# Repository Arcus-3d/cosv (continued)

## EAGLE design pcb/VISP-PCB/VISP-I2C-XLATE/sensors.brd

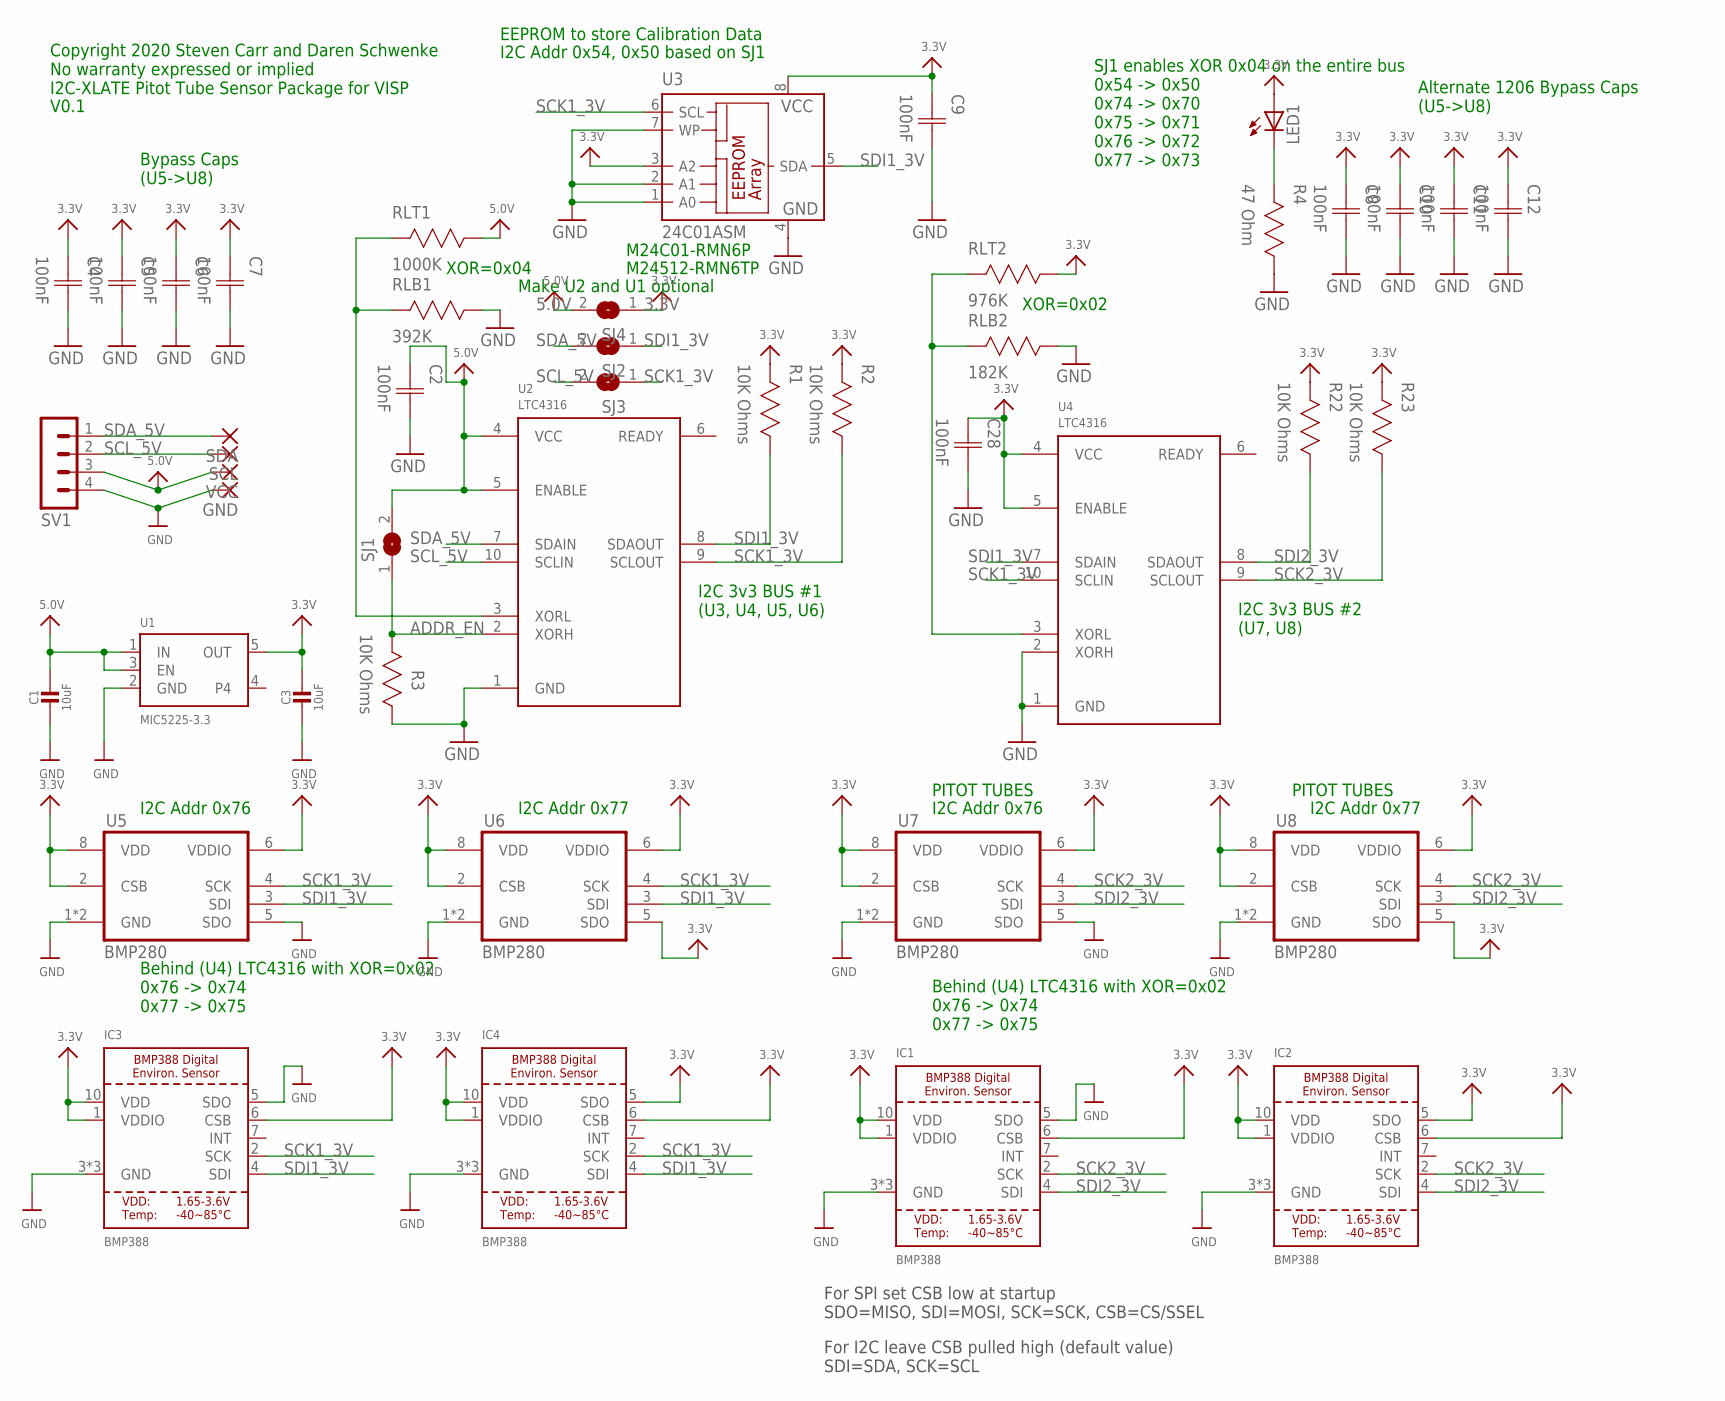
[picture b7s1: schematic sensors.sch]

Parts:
C1, C3: 10uF; 0603-NO; MPN C1608X5R1A106M080AC
C2, C9, C28: 100nF; CAP0603; MPN CL10B104KB8NNNC
C4, C5, C6, C7: 100nF; CAP0402; MPN CL10F104ZO8NNNC
C8, C10, C11, C12: 100nF; CAP1206; MPN C1206C104K5RAC7800
GND: SMD2; SMD1,27-2,54
IC1, IC2, IC3, IC4: BMP388; MPN BMP388
LED1: LEDCHIP-LED0603; CHIP-LED0603; MPN SML-D12P8WT86
R1, R2, R22, R23: 10K Ohms; RES0603; MPN CRCW060310K0FKEAC
R3: 10K Ohms; RES0603; MPN CL10B104KB8NNNC
R4: 47 Ohm; RES0603; MPN RC0603FR-0747RL
RLB1: 392K; RES0603; MPN RC0603FR-07392KL
RLB2: 182K; RES0603; MPN RC0603FR-07182KL
RLT1: 1000K; RES0603; MPN CRCW060310K0FKEAC
RLT2: 976K; RES0603; MPN RC0603FR-07976KL
SCL: SMD2; SMD1,27-2,54
SDA: SMD2; SMD1,27-2,54
SJ1, SJ2, SJ3, SJ4: SJ
SV1: MA04-1
U1: MIC5225-3.3; SOT23-5; MPN MIC5225-3.3YM5-TR
U2, U4: LTC4316; MSOP10; MPN LTC4316IMS#PBF
U3: 24C01ASM; SO-08M; MPN M24C01-RMN6P
U5, U6, U7, U8: BMP280; MPN BMP280
VCC: SMD2; SMD1,27-2,54

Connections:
3.3V: C3.1, C4.1 (C1), C5.1 (C1), C6.1 (C1), C7.1 (C1), C8.1 (C1), C9.1 (C1), C10.1 (C1), C11.1 (C1), C12.1 (C1), C28.1 (C1), IC1.1 (VDDIO), IC1.6 (CSB), IC1.10 (VDD), IC2.1 (VDDIO), IC2.5 (SDO), IC2.6 (CSB), IC2.10 (VDD), IC3.1 (VDDIO), IC3.6 (CSB), IC3.10 (VDD), IC4.1 (VDDIO), IC4.5 (SDO), IC4.6 (CSB), IC4.10 (VDD), LED1.A, R1.2, R2.2, R22.2, R23.2, RLT2.1, SJ4.1, U1.5 (OUT), U3.3 (A2), U3.8 (VCC), U4.4 (VCC), U4.5 (ENABLE), U5.2 (CSB), U5.6 (VDDIO), U5.8 (VDD), U6.2 (CSB), U6.5 (SDO), U6.6 (VDDIO), U6.8 (VDD), U7.2 (CSB), U7.6 (VDDIO), U7.8 (VDD), U8.2 (CSB), U8.5 (SDO), U8.6 (VDDIO), U8.8 (VDD)
5.0V: C1.1, C2.1 (C1), RLT1.1, SJ1.2, SJ4.2, SV1.3, U1.1 (IN), U1.3 (EN), U2.4 (VCC), U2.5 (ENABLE), VCC.1
ADDR_EN: R3.2, SJ1.1, U2.2 (XORH)
GND: C1.2, C2.2 (C2), C3.2, C4.2 (C2), C5.2 (C2), C6.2 (C2), C7.2 (C2), C8.2 (C2), C9.2 (C2), C10.2 (C2), C11.2 (C2), C12.2 (C2), C28.2 (C2), GND.1, IC1.3 (GND), IC1.5 (SDO), IC1.8 (GND), IC1.9 (GND), IC2.3 (GND), IC2.8 (GND), IC2.9 (GND), IC3.3 (GND), IC3.5 (SDO), IC3.8 (GND), IC3.9 (GND), IC4.3 (GND), IC4.8 (GND), IC4.9 (GND), R3.1, R4.1, RLB1.1, RLB2.1, SV1.4, U1.2 (GND), U2.1 (GND), U3.1 (A0), U3.2 (A1), U3.4 (GND), U3.7 (WP), U4.1 (GND), U4.2 (XORH), U5.1 (GND), U5.5 (SDO), U5.7 (GND), U6.1 (GND), U6.7 (GND), U7.1 (GND), U7.5 (SDO), U7.7 (GND), U8.1 (GND), U8.7 (GND)
LED: LED1.C, R4.2
SCK1_3V: IC3.2 (SCK), IC4.2 (SCK), R2.1, SJ3.1, U2.9 (SCLOUT), U3.6 (SCL), U4.10 (SCLIN), U5.4 (SCK), U6.4 (SCK)
SCK2_3V: IC1.2 (SCK), IC2.2 (SCK), R23.1, U4.9 (SCLOUT), U7.4 (SCK), U8.4 (SCK)
SCL_5V: SCL.1, SJ3.2, SV1.2, U2.10 (SCLIN)
SDA_5V: SDA.1, SJ2.2, SV1.1, U2.7 (SDAIN)
SDI1_3V: IC3.4 (SDI), IC4.4 (SDI), R1.1, SJ2.1, U2.8 (SDAOUT), U3.5 (SDA), U4.7 (SDAIN), U5.3 (SDI), U6.3 (SDI)
SDI2_3V: IC1.4 (SDI), IC2.4 (SDI), R22.1, U4.8 (SDAOUT), U7.3 (SDI), U8.3 (SDI)
XORL1: RLB1.2, RLT1.2, U2.3 (XORL)
XORL2: RLB2.2, RLT2.2, U4.3 (XORL)

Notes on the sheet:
XOR=0x02
XOR=0x04
Bypass Caps (U5->U8)
Copyright 2020 Steven Carr and Daren Schwenke No warranty expressed or implied I2C-XLATE Pitot Tube Sensor Package for VISP
EEPROM to store Calibration Data
I2C Addr 0x54, 0x50 based on SJ1
I2C Addr 0x76
I2C Addr 0x77
Behind (U4) LTC4316 with XOR=0x02 0x76 -> 0x74 0x77 -> 0x75
SJ1 enables XOR 0x04 on the entire bus 0x54 -> 0x50 0x74 -> 0x70 0x75 -> 0x71 0x76 -> 0x72 0x77 -> 0x73
I2C 3v3 BUS #1 (U3, U4, U5, U6)
I2C 3v3 BUS #2 (U7, U8)
V0.1
Make U2 and U1 optional
PITOT TUBES
For SPI set CSB low at startup SDO=MISO, SDI=MOSI, SCK=SCK, CSB=CS/SSEL
For I2C leave CSB pulled high (default value) SDI=SDA, SCK=SCL
Alternate 1206 Bypass Caps (U5->U8)
M24C01-RMN6P
M24512-RMN6TP

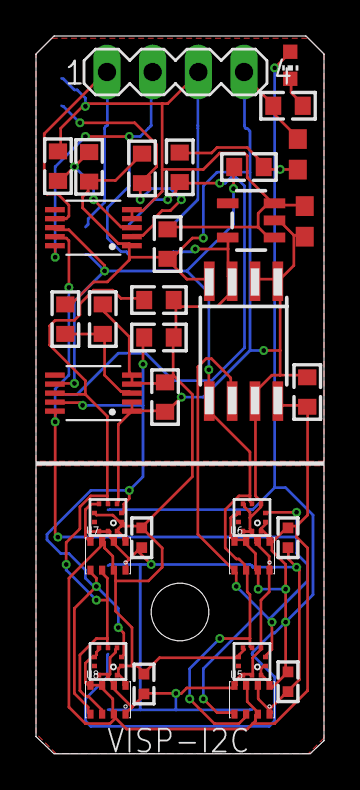
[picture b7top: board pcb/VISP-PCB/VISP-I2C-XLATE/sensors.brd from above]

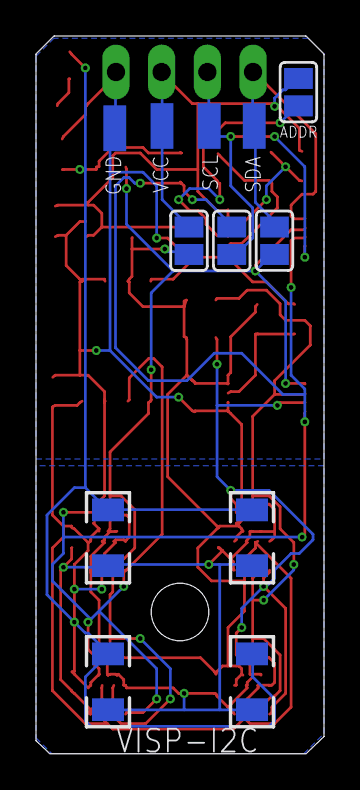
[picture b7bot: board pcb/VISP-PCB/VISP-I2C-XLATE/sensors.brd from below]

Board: 2 copper layers, 16.0 x 39.9 mm, 45 parts (12 on the bottom side), 13 nets.

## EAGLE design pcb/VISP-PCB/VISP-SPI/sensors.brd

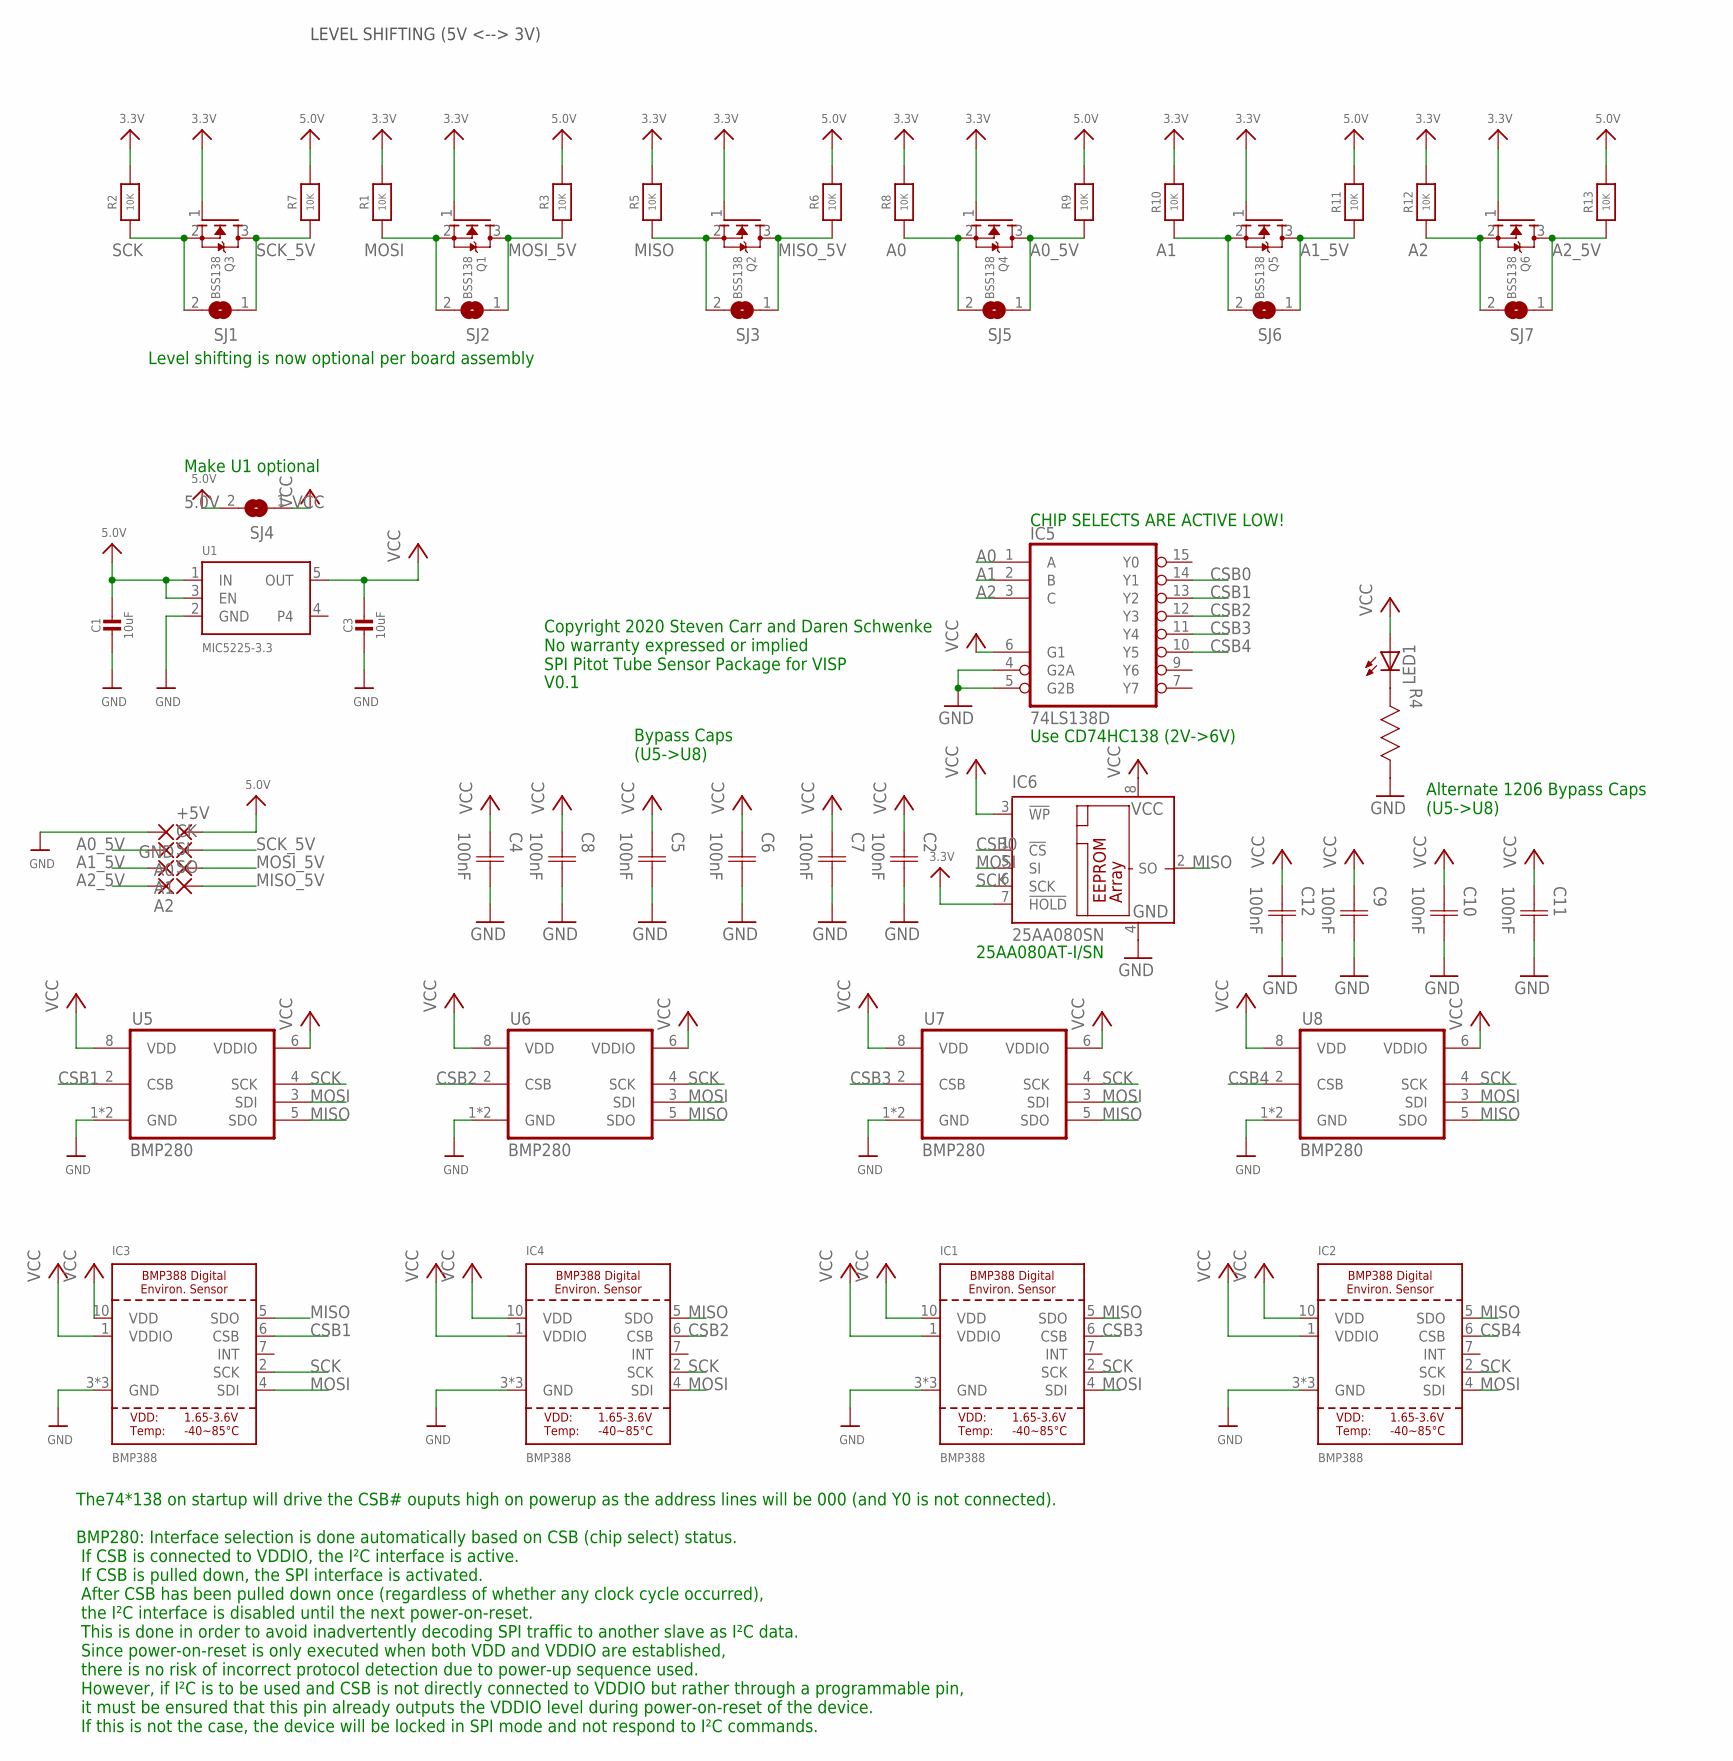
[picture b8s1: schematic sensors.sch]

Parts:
+5V: SMD2; SMD1,27-2,54
A0, A1, A2: SMD2; SMD1,27-2,54
C1, C3: 10uF; 0603-NO
C2, C4, C5, C6, C7, C8: 100nF; CAP0402
C9, C10, C11, C12: 100nF; CAP1206
CK: SMD2; SMD1,27-2,54
GND: SMD2; SMD1,27-2,54
IC1, IC2, IC3, IC4: BMP388
IC5: 74LS138D; SO16; MPN CD74LS138D
IC6: 25AA080SN; SO-08
LED1: LEDCHIP-LED0603; CHIP-LED0603
Q1, Q2, Q3, Q4, Q5, Q6: BSS138; SOT23-WIDE
R1, R2, R3, R5, R6, R7, R8, R9, R10, R11, R12, R13: 10K; 0805-NO
R4: RESISTOR-0603; RES0603
SI: SMD2; SMD1,27-2,54
SJ1, SJ2, SJ3, SJ4, SJ5, SJ6, SJ7: SJ
SO: SMD2; SMD1,27-2,54
U1: MIC5225-3.3; SOT23-5
U5, U6, U7, U8: BMP280

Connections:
3.3V: IC6.7 (!HOLD), Q1.1 (G), Q2.1 (G), Q3.1 (G), Q4.1 (G), Q5.1 (G), Q6.1 (G), R1.2, R2.2, R5.2, R8.2, R10.2, R12.2
5.0V: +5V.1, C1.1, R3.2, R6.2, R7.2, R9.2, R11.2, R13.2, SJ4.2, U1.1 (IN), U1.3 (EN)
A0: IC5.1 (A), Q4.2 (S), R8.1, SJ5.2
A0_5V: A0.1, Q4.3 (D), R9.1, SJ5.1
A1: IC5.2 (B), Q5.2 (S), R10.1, SJ6.2
A1_5V: A1.1, Q5.3 (D), R11.1, SJ6.1
A2: IC5.3 (C), Q6.2 (S), R12.1, SJ7.2
A2_5V: A2.1, Q6.3 (D), R13.1, SJ7.1
CSB0: IC5.14 (Y1), IC6.1 (!CS)
CSB1: IC3.6 (CSB), IC5.13 (Y2), U5.2 (CSB)
CSB2: IC4.6 (CSB), IC5.12 (Y3), U6.2 (CSB)
CSB3: IC1.6 (CSB), IC5.11 (Y4), U7.2 (CSB)
CSB4: IC2.6 (CSB), IC5.10 (Y5), U8.2 (CSB)
GND: C1.2, C2.2 (C2), C3.2, C4.2 (C2), C5.2 (C2), C6.2 (C2), C7.2 (C2), C8.2 (C2), C9.2 (C2), C10.2 (C2), C11.2 (C2), C12.2 (C2), GND.1, IC1.3 (GND), IC1.8 (GND), IC1.9 (GND), IC2.3 (GND), IC2.8 (GND), IC2.9 (GND), IC3.3 (GND), IC3.8 (GND), IC3.9 (GND), IC4.3 (GND), IC4.8 (GND), IC4.9 (GND), IC5.4 (G2A), IC5.5 (G2B), IC5.8 (GND), IC6.4 (GND), R4.1, U1.2 (GND), U5.1 (GND), U5.7 (GND), U6.1 (GND), U6.7 (GND), U7.1 (GND), U7.7 (GND), U8.1 (GND), U8.7 (GND)
MISO: IC1.5 (SDO), IC2.5 (SDO), IC3.5 (SDO), IC4.5 (SDO), IC6.2 (SO), Q2.2 (S), R5.1, SJ3.2, U5.5 (SDO), U6.5 (SDO), U7.5 (SDO), U8.5 (SDO)
MISO_5V: Q2.3 (D), R6.1, SJ3.1, SO.1
MOSI: IC1.4 (SDI), IC2.4 (SDI), IC3.4 (SDI), IC4.4 (SDI), IC6.5 (SI), Q1.2 (S), R1.1, SJ2.2, U5.3 (SDI), U6.3 (SDI), U7.3 (SDI), U8.3 (SDI)
MOSI_5V: Q1.3 (D), R3.1, SI.1, SJ2.1
unnamed: LED1.C, R4.2
SCK: IC1.2 (SCK), IC2.2 (SCK), IC3.2 (SCK), IC4.2 (SCK), IC6.6 (SCK), Q3.2 (S), R2.1, SJ1.2, U5.4 (SCK), U6.4 (SCK), U7.4 (SCK), U8.4 (SCK)
SCK_5V: CK.1, Q3.3 (D), R7.1, SJ1.1
VCC: C2.1 (C1), C3.1, C4.1 (C1), C5.1 (C1), C6.1 (C1), C7.1 (C1), C8.1 (C1), C9.1 (C1), C10.1 (C1), C11.1 (C1), C12.1 (C1), IC1.1 (VDDIO), IC1.10 (VDD), IC2.1 (VDDIO), IC2.10 (VDD), IC3.1 (VDDIO), IC3.10 (VDD), IC4.1 (VDDIO), IC4.10 (VDD), IC5.6 (G1), IC5.16 (VCC), IC6.3 (!WP), IC6.8 (VCC), LED1.A, SJ4.1, U1.5 (OUT), U5.6 (VDDIO), U5.8 (VDD), U6.6 (VDDIO), U6.8 (VDD), U7.6 (VDDIO), U7.8 (VDD), U8.6 (VDDIO), U8.8 (VDD)

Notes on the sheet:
Bypass Caps (U5->U8)
Copyright 2020 Steven Carr and Daren Schwenke No warranty expressed or implied SPI Pitot Tube Sensor Package for VISP
V0.1
Make U1 optional
CHIP SELECTS ARE ACTIVE LOW!
Use CD74HC138 (2V->6V)
Alternate 1206 Bypass Caps (U5->U8)
25AA080AT-I/SN
The74*138 on startup will drive the CSB# ouputs high on powerup as the address lines will be 000 (and Y0 is not connected). BMP280: Interface selection is done automatically based on CSB (chip select) status. If CSB is connected to VDDIO, the I²C interface is active. If CSB is pulled down, the SPI 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
LEVEL SHIFTING (5V <--> 3V)
Level shifting is now optional per board assembly

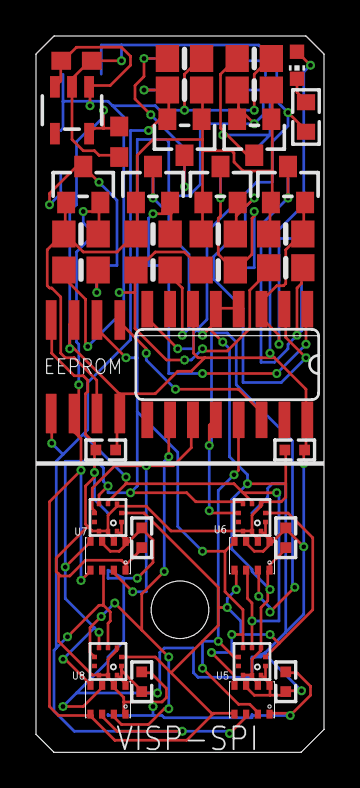
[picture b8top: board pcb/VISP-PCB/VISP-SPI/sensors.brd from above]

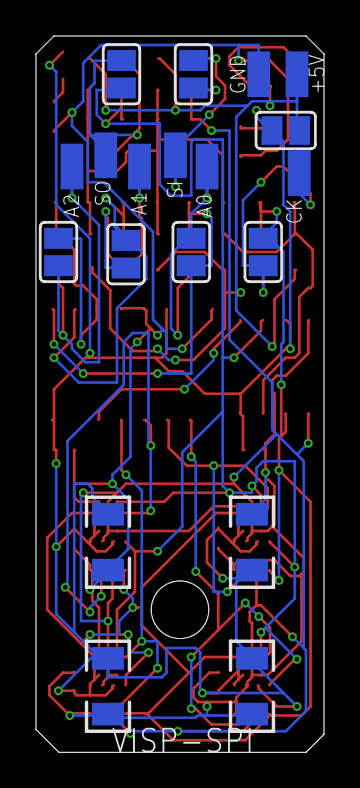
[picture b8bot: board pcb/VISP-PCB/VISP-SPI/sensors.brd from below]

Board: 2 copper layers, 16.0 x 39.8 mm, 58 parts (19 on the bottom side), 22 nets.

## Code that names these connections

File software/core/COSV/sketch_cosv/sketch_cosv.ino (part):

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// A5 - OLED SCL

//
// PD0 - RX - To GUI Processor
// PD1 - TX - To GUI Processor
int VAPE_IN  = 2; // PD2 - IRQ Digital Input - Cheap Vape Sensor (for now)
int BLDC_FG  = 3; // PD3 - IRQ Digital Input - Motor FG
int BLDC_DIR = 4; // PD4 -            - BLDC Motor Direction
int BLDC_PWM = 5; // PD5 - PWM Output - BLDC Motor speed
int WATCHDOG = 6; // PD6 - Watchdog output pulse
int HOME_SENSOR = 7; // PD7 - Digital Input Home Sensor (Pulled up internally, connect other sensor lead to GND)

int STEP_P0 = 8;
int STEP_P1 = 9;
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

//
// PB2 - SS   -
// PB3 - MISO -
// PB4 - MOSI -
// PB5 - SCK  - Also built in uno led...
int LED = 13;

// Hardware
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
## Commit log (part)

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2020-03-25 initial upload
2020-03-25 add gitignore
2020-03-25 moved stuff to allow software
2020-03-25 labeled stuff
2020-03-25 smaller body, less bolts
2020-03-25 softened base corner, rendered for bldc
2020-03-25 renamed output to rendered
2020-03-25 changes for rendering laser files
2020-03-25 bldc motor standoff
2020-03-25 more rendered output files
2020-03-25 more renders
2020-03-27 FFF cam was too short since exploding
2020-03-28 new arms for milling from plywood
2020-03-28 ports didn't go through
2020-03-29 updates for cover and chips of sensor
2020-03-29 renders for milling
2020-03-30 flow sensor body done!
2020-03-30 fixed path for pitot, cover work
2020-03-31 rendered the paddles
2020-03-31 SLA version with no bevel
2020-04-05 Added software, commented source, flow_test part
2020-04-05 VISP pcb files
2020-04-05 clipped version for oversize test PCB
2020-04-08 laser washers and paddle name
2020-04-10 pcb now 20mm wide
2020-04-15 rendered FFF for threaded rod/thicker arm
2020-04-15 linefeed test
2020-04-16 re-rendered to ensure these are up to date
2020-04-23 kivy graph
2020-04-23 touch work
2020-04-24 More touch work
2020-04-25 Got class, ini trial
2020-04-25 touch binding too fast
2020-04-25 Tuning touch events for multi
2020-04-27 core testing work + UI
2020-04-27 I2C Bus and Discovery enhancements
    1) Added support for I2C bus enabling using NPN transistors
    Supports Dual I2C VISP with a single I2C port
    2) Cleaned up sensor detection algorithms
    Match sensor to #defines for consistent use in upper levels
    3) Enable transparent TEENSY Serial1 vs NANO Serial outputs (one place to mod)
    4) Simplify I2C second bus vs Enabled clocks for Dual I2C VISP access
2020-04-27 flow work
2020-04-27 I2C Mux Channel Cleanup
    Remove Mux Channel debugging
    Preserve Mux Channel state to reduce unnecessary I2C IO
2020-04-28 Introduce initial support for EEPROM settings
    Also, ne spot for Venturi code to live, and move Pitot code to it's own function
2020-04-28 Introduce new Venturi VISP
2020-04-28 Make debug output logging optional at compile time
2020-04-28 All constants that deal with floats are now floats as well Clear calibration data on start, and on forced calibration
2020-04-28 Add ability to read/write to the EEPROM on the VISP PCB
2020-04-29 scrollable graphs work
2020-04-29 Add debugging to prove SPL06 sensor calibration is unique to each sensor
2020-04-29 Configure SPL06 to sample 128 times a second with 8X oversampling
    This brings the SPL06 sensor reading frequency in line with the BMP280
2020-04-29 Correct I2C enable pins for busWriteBuf()
2020-04-29 UI tuning and visp param
2020-04-30 tidalVolume moved to core
2020-04-30 motor test
2020-04-30 UI test
2020-04-30 Add support for the BMP388 sensor
2020-04-30 Remove "Data Is Ready" output that was used for BMP388 testing
2020-05-01 State work
2020-05-01 Add Communications IO document for VISP Core Processor Serial IO
2020-05-01 Permit Q to inform the display about min/max/dict for settings
2020-05-01 UI work
2020-05-01 UI event test
2020-05-01 UI testing
2020-05-02 Nano uses %S to read from flash memory (Harvard Architecture) Teensy uses %s to read from flash memory (Von Neumann Architecture)
2020-05-02 new laser arms
2020-05-02 milling arm
2020-05-03 Improve debug state handling
2020-05-03 Properly respond to read-only settings, like discovered sensor types
2020-05-03 Only toggle pulse pin if system health is good
2020-05-03 UI for demo updates
2020-05-03 UI updates for demo
2020-05-04 Automate the generation of STL, SVG, and DXF files
2020-05-04 Move some motor pins around
2020-05-04 new paddle
2020-05-04 Fine tune the motor homing code
2020-05-04 Switch to micros() in homeThisPuppy()
2020-05-05 Generate all cam and base plate types for the different motors available Also, make the scad file thingiverse compatible for customization
2020-05-05 Testing
2020-05-06 Reduction in compiled code space, and initial motor calibration
    Refactor command parser to be table driven
    Eliminate malloc() and free() to remove memory fragmentation issues
    Added motor calibration
    Parameter updates to match the interface (rate in Breaths/min and I:E as a scale factor)
    Eliminated snprintf_P to reduce code size by approximately 2KB
    Cleaned up some compiler warnings for NANO/UNO
2020-05-06 Correct Teensy 4.0 compiler errors/warnings
2020-05-07 Correct "Unterminated string" error from Makefile
2020-05-07 Additional refactoring. Also added in new settings response for *_display enable/disable based on active mode Removed Ping command, 'H'ealth Status does the same thing.
2020-05-08 Refactoring continued.
2020-05-08 Add Kivy setup instructions
2020-05-08 Motor work
    Pins have been moved/consolidated.
    Motor control pins have been reduced to 4 and handle BLDC, STEPPER and generic H-Bridge DC motors.
    Put motor code into separate files.
    Motor detection algoritm is now a state machine and permits command IO during detection.
    Add CPU Utilization code for debug output
2020-05-10 Massive changes to body. Tab/slot assembly.
2020-05-10 More non cut parts in physical form for clearance.
2020-05-10 HELP ME PICK AN OSHW LICENSE. Please.
2020-05-10 Laser files and paddle rendered
2020-05-10 less material paddle
2020-05-11 led hole correction, new renders
2020-05-11 Actually render the changes..
2020-05-11 Actually render the files, again.
2020-05-11 moved the motor cutout the wrong way..
2020-05-12 Enhanced motor detection algorithm. Added STM32 target "Blue Pill".
2020-05-12 cam encoder
2020-05-12 Refined motor control settings. motor_* settings have been added to the command interpreter which permits testing in a controlled environment.
    Also, motor_speed has been brought back.
2020-05-13 New enable function callback for bus devices.
    Permits the unorthodox use of multiple pins to select a device/bus
    Example: using a 3-to-8 decoder to individually select an SPI peripheral
2020-05-13 Flash space savings, down to 91% on the Arduino Nano
    Integrate stepper code saves space by not having modes we do not use.
    Also prepping for interrupt driven stepper control for smoother operation of the motor.
2020-05-15 dimension tweaks, removable front/back, encoder
2020-05-15 Update the protocol documentation
2020-05-15 Add support for dual I2C displays for some output of what is going on
2020-05-15 TEENSY 4.0 Dual I2C is now workign properly. Display code has been updated to handle disconnecting/reconecting OLEDs
2020-05-16 dimension tweaks
2020-05-18 centered home, encoder with through nuts
2020-05-20 Show the sensor types on the right hand side for now, testing interface code
2020-05-20 Introducing a simplified core monitor written in FLTK
2020-05-21 Convert chart to time based, and add second tick marks
2020-05-21 Correct button height computation on menu popups
2020-05-21 Support core sending button fgcolor and bgcolor with color names The goal is to support button alerts to indicate problems
2020-05-21 Big red X across the whole screen if the core reports being bad
2020-05-21 New motor identification algorithm designed to use the encoder Now, only HBRIDGE or STEPPER variants supported.
2020-05-21 Remove leading spaces in front of sensor calibration output Also, side benefit of saving 1.5K of code space by not using dtostrf()
2020-05-22 Core EEPROM saving enhancements.
    Migrate the apropriate settings to the ATMEGA EEPROM.
    Fixed setting of 8-bit values (pointer was treated as int16)
    (Compiled code still fits in an Arduino UNO)
2020-05-22 Update the LCD displays in an interleave fashion
    Stop hogging the CPU trying to update the screens!
2020-05-22 Don't pummel the core with rapid changes in slider settings Only send when the popup is dismissed
2020-05-22 Debug now displays expert buttons Like setting mode parameters and the like
2020-05-23 Display Critical alerts in titlebar, handle new Q response to ensure icon ordering
2020-05-23 Add a Begin/End to the Q output so the front end knows when the S list starts and ends
2020-05-24 battery mounts, encoder tweaks
2020-05-24 laser files cleanup
2020-05-24 kerf tester strip
2020-05-24 rendered for kerf 0.04
2020-05-24 generated wrong item
2020-05-24 Automate the generation of DXF and SVG files for future automated panelization
2020-05-26 Gracefully handle connecting/disconnecting the VISP PCB from the core
    eeprom was not being Free'd upon partial sensor scan
2020-05-26 Use fixed busDevice buffers instead of dynamic
2020-05-27 New TEENSY 4.0 carrier board for COSV Supports both analog+2.8" SPI display and rPi interfaces Also, supports rPi only mode of operation with solder jumper (sans battery level monitoring)
2020-05-28 Save some more space for hardware monitoring
2020-05-28 Make the motor connector identical to the Arduino IBT_2 H-Bridge
2020-05-28 dir cleanup
2020-05-28 Add Line Power Detect input and Watchdog Pulse output for alarm subsystem
2020-06-03 Initial support for remote passthrough for nurse station monitoring over TCPIP
2020-06-12 Correct motor control scaling bugs
2020-06-12 Add support for remote viewing (aka Nurses monitoring station)
2020-06-12 Add /dev/ttyS0 detection to flcosvmon for rPi 3/4 interface
2020-06-15 Round the corners a bit more to keep from getting hit by the cam arm
2020-06-22 JLCPCB Proven - Dual I2C board with BMP280/SLP06-007 footprints
2020-06-22 Snap In Photo Interrupter Enhancements.
2020-06-23 Add plateau identification in charts
2020-07-04 New "millable" Carrier board for use with rPI3+ on COSV
2020-07-04 Updated core todo list
2020-07-04 Motor run state machine to assist in identifying failure modes
2020-07-04 Proper battery level monitoring. CPU agnostic approach. Permits R1 and R2 changing in the config.h for your carrier board
2020-08-24 New! Teensy 4.0 Carrier board with analog support This bord supports standalone mode using analog pots to control everything.
2020-08-25 Update VISP-I2C-MUX for manufacturing by OSH-Park All 8 sensor pads can be populated simultaneously without I2C bus conflicts. Updated board text to reflect new capabilities Increased width slightly 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
2020-08-25 Routed for easier milling
2020-08-25 v7 export
2020-09-01 Enlarge labels to make them readable by humans on the VISP-I2C-MUX PCB
2020-09-01 Update Label: Pullup resistors are 2K7 on the downstream I2C buses
2020-09-04 Interrupt once we get past the home opening, the next time we turn the motor on, we won't see a reflection and think we are home.
2020-09-04 For now, pretend that we are always on mains power
2020-09-18 New BMP388-only I2C MUX board, the latest (and greatest) board for the VISP.
    Now, each of the 4 sensors are on separate I2C buses.
2020-09-22 Remove temporary eagle file
2020-09-22 Update notes in schematics for VISP PCB's
2020-09-29 Add eagle 9.6.2 version of visp for board manufacturing
2020-10-09 New flow sensor for CO2
2020-10-09 Increase GUI interface serial baud speed to match new core speed
2020-10-12 Correct unsigned long comparison to -1 for time to stop breathing
2020-10-12 Revert back to 115200 baud
2020-10-13 Exploded view work
2020-10-14 Correct computation for 1:2 is really 33%:66% not 50%:50%
2020-10-14 tidalVolume averaging and motor work
2020-10-14 Do not block on writing to a remoteFd just drop the connection if they do not consume enough (network issues?)
2020-10-14 Ignore interrupts from Home Position if we had recently "gone home"
2020-10-14 Initial attempt at using FastPID library for motor control
2020-10-14 motor max speed setting
2020-10-16 Default to exploded view
2020-10-18 renders for presentation base
2020-10-22 moving forward? I don't remember..
2020-10-22 ONE thing done. :)
2020-10-23 Enlarge min/max range slider window to make it easier to use with fingers
2020-10-23 Make the window full screen
2020-10-23 Title/Error output now visible when fullscreen on rPi
